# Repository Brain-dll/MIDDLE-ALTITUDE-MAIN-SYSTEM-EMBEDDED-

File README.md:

# technofest-3000-telemetry
This repository was created to improve telemetry system of Ephemeris

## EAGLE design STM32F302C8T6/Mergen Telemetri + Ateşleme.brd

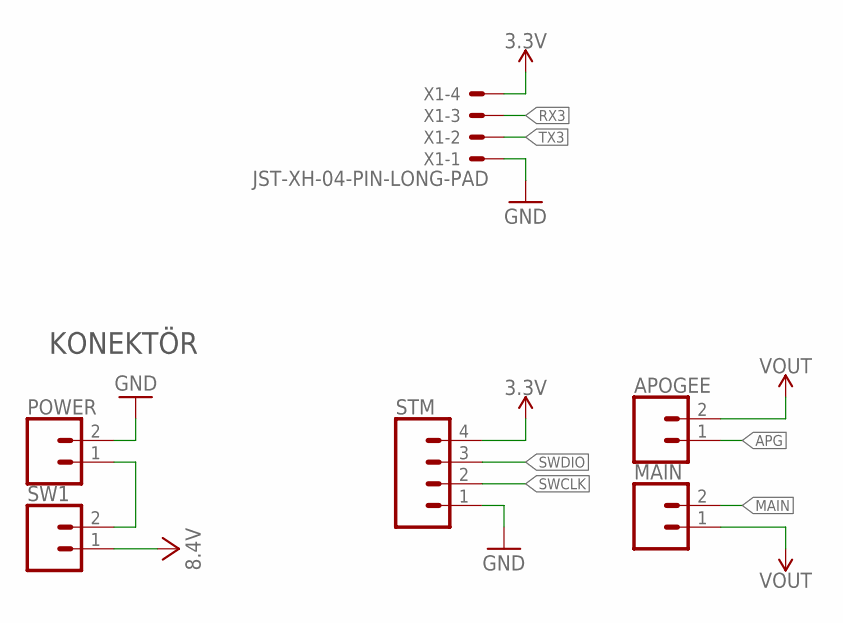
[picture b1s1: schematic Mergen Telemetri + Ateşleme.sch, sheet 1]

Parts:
APOGEE: CONN_023.5MM-NO_SILK; SCREWTERMINAL-3.5MM-2-NS
MAIN: CONN_023.5MM-NO_SILK; SCREWTERMINAL-3.5MM-2-NS
POWER: CONN_023.5MM-NO_SILK; SCREWTERMINAL-3.5MM-2-NS
STM: CONN_04; 1X04
SW1: CONN_023.5MM-NO_SILK; SCREWTERMINAL-3.5MM-2-NS
X1: JST-XH-04-PIN-LONG-PAD; JST-XH-04-PACKAGE-LONG-PAD

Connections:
3.3V: STM.4, X1.4; also elsewhere on the board
APG: APOGEE.1; also elsewhere on the board
GND: POWER.2, STM.1, X1.1; also elsewhere on the board
MAIN: MAIN.2; also elsewhere on the board
unnamed: POWER.1, SW1.2
RX3: X1.3; also elsewhere on the board
SWCLK: STM.2; also elsewhere on the board
SWDIO: STM.3; also elsewhere on the board
TX3: X1.2; also elsewhere on the board
VCC: SW1.1; also elsewhere on the board
VOUT: APOGEE.2, MAIN.1; also elsewhere on the board

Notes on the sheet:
KONEKTÖR

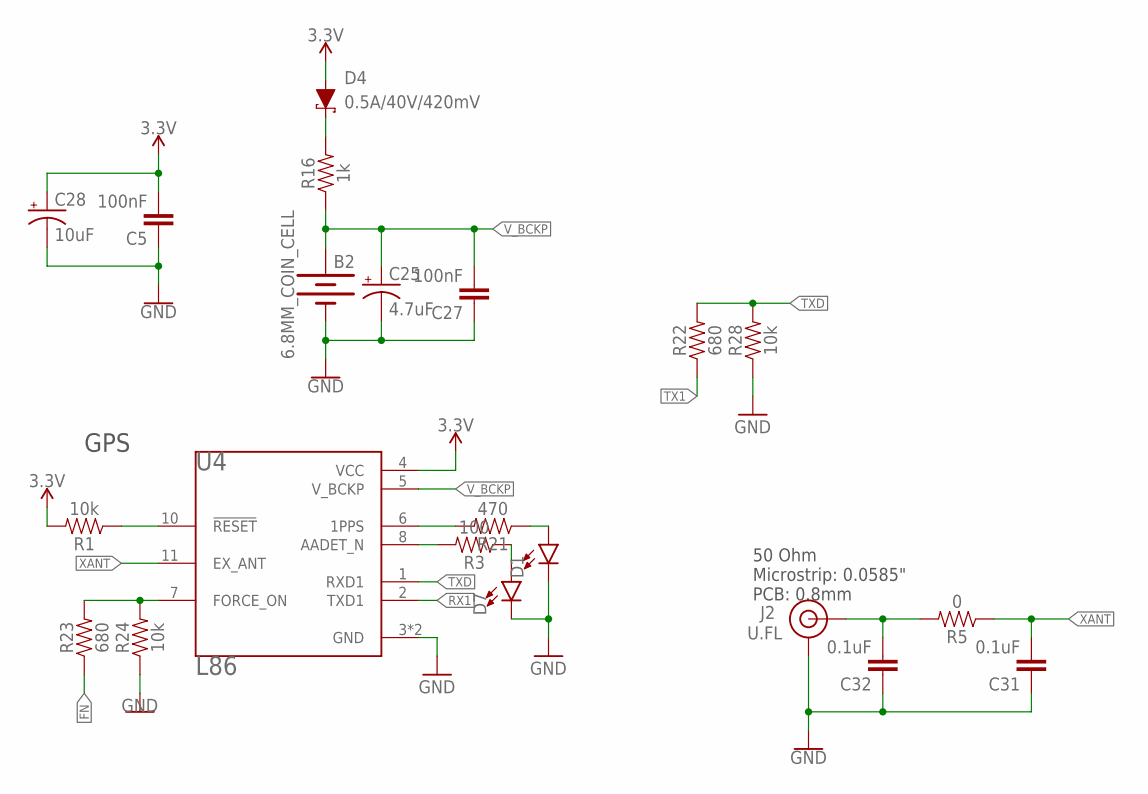
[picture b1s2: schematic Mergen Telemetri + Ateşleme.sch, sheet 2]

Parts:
B2: 6.8MM_COIN_CELL; BATTCON-6.8MM
C5, C27: 100nF; 0603
C25: 4.7uF; EIA3216
C28: 10uF; EIA3216
C31, C32: 0.1uF; 0603
D1, D7: LED0603; LED-0603
D4: 0.5A/40V/420mV; SOD-323
J2: U.FL
R1, R24, R28: 10k; 0603
R3: 100; 0603
R5: 0; 0603
R16: 1k; 0603
R21: 470; 0603
R22, R23: 680; 0603
U4: L86; XCVR_L86

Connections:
3.3V: C5.2, C28.+, D4.A, R1.2, U4.4 (VCC); also elsewhere on the board
FN: R23.1; also elsewhere on the board
GND: B2.-, C5.1, C25.-, C27.1, C28.-, C31.1, C32.1, D1.C, D7.C, J2.1 (GND), J2.2 (GND), R24.1, R28.1, U4.3 (GND), U4.12 (GND); also elsewhere on the board
unnamed: R1.1, U4.10 (!RESET)
unnamed: R21.2, U4.6 (1PPS)
unnamed: D1.A, R21.1
unnamed: D4.C, R16.2
unnamed: R3.2, U4.8 (AADET_N)
unnamed: D7.A, R3.1
unnamed: C32.2, J2.FEED (SIGNAL), R5.2
unnamed: R23.2, R24.2, U4.7 (FORCE_ON)
RX1: U4.2 (TXD1); also elsewhere on the board
TX1: R22.1; also elsewhere on the board
TXD: R22.2, R28.2, U4.1 (RXD1)
V_BCKP: B2.+, C25.+, C27.2, R16.1, U4.5 (V_BCKP)
XANT: C31.2, R5.1, U4.11 (EX_ANT)

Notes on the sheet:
GPS
50 Ohm Microstrip: 0.0585" PCB: 0.8mm

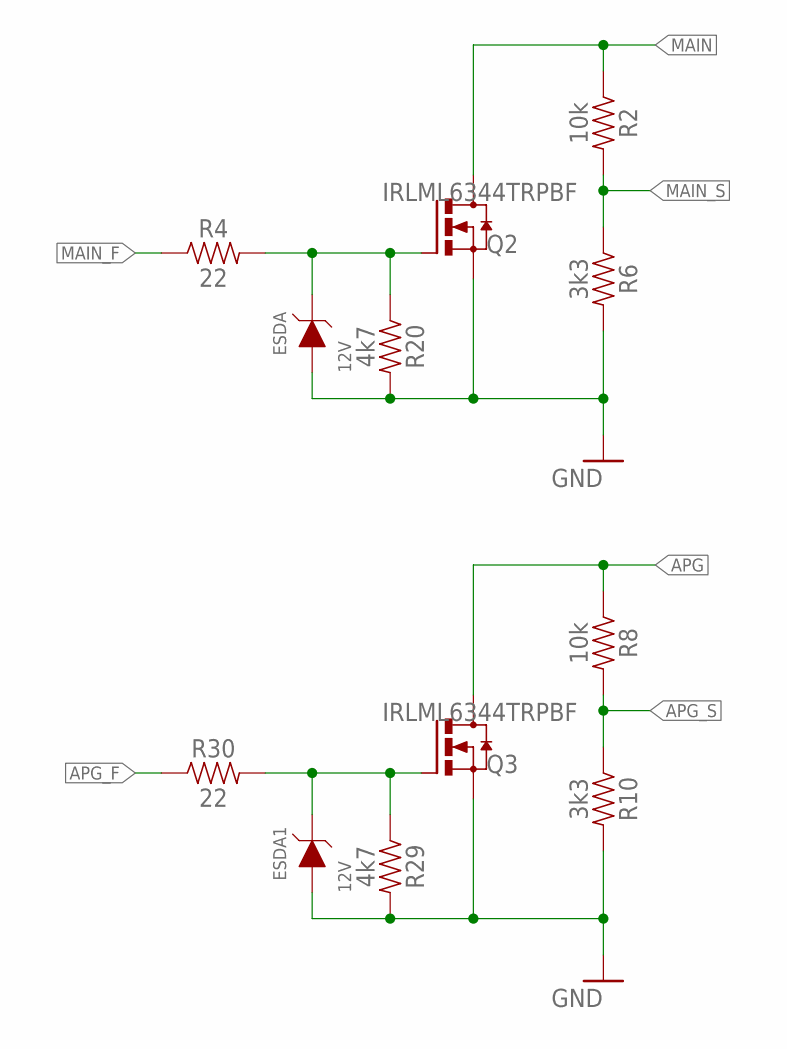
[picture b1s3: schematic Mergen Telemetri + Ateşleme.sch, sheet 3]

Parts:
ESDA, ESDA1: 12V; WE-TVSP_DO-214AC_UNIDIRECTIONAL
Q2, Q3: IRLML6344TRPBF; SOT23
R2, R8: 10k; 0603
R4, R30: 22; 0603
R6, R10: 3k3; 0603
R20, R29: 4k7; 0603

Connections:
APG: Q3.3 (D), R8.1; also elsewhere on the board
APG_F: R30.1; also elsewhere on the board
APG_S: R8.2, R10.1; also elsewhere on the board
GND: ESDA.2 (A), ESDA1.2 (A), Q2.2 (S), Q3.2 (S), R6.2, R10.2, R20.2, R29.2; also elsewhere on the board
MAIN: Q2.3 (D), R2.1; also elsewhere on the board
MAIN_F: R4.1; also elsewhere on the board
MAIN_S: R2.2, R6.1; also elsewhere on the board
unnamed: ESDA1.1 (C), Q3.1 (G), R29.1, R30.2
unnamed: ESDA.1 (C), Q2.1 (G), R4.2, R20.1

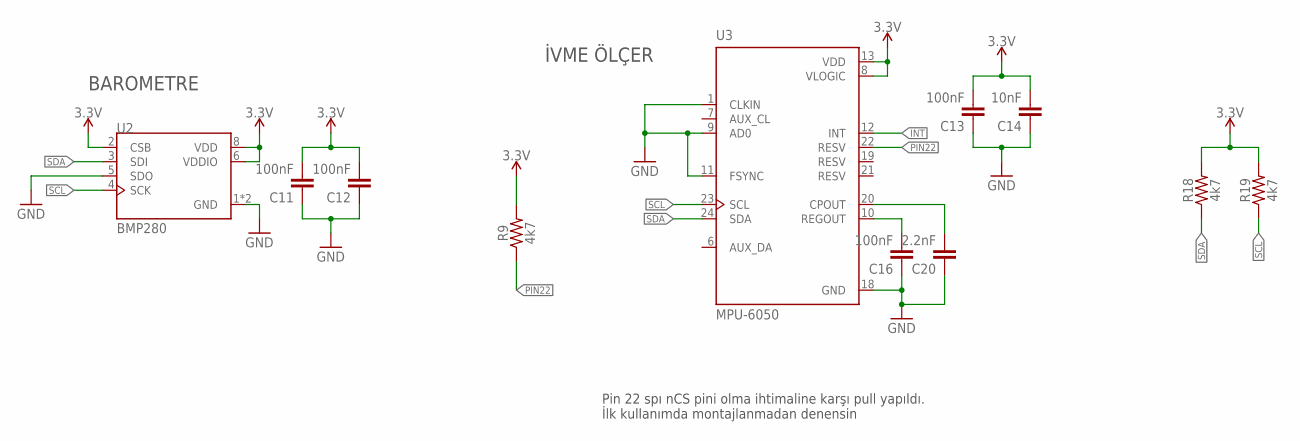
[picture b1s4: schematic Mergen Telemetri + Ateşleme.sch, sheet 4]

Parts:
C11, C12, C13, C16: 100nF; 0603
C14: 10nF; 0603
C20: 2.2nF; 0603
R9, R18, R19: 4k7; 0603
U2: BMP280; XDCR_BMP280
U3: MPU-6050; QFN50P400X400X95-24N

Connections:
3.3V: C11.2, C12.2, C13.2, C14.2, R9.2, R18.2, R19.2, U2.2 (CSB), U2.6 (VDDIO), U2.8 (VDD), U3.8 (VLOGIC), U3.13 (VDD); also elsewhere on the board
GND: C11.1, C12.1, C13.1, C14.1, C16.1, C20.1, U2.1 (GND), U2.5 (SDO), U2.7 (GND), U3.1 (CLKIN), U3.9 (AD0), U3.11 (FSYNC), U3.18 (GND); also elsewhere on the board
INT: U3.12 (INT); also elsewhere on the board
unnamed: C16.2, U3.10 (REGOUT)
unnamed: C20.2, U3.20 (CPOUT)
PIN22: R9.1, U3.22 (RESV)
SCL: R19.1, U2.4 (SCK), U3.23 (SCL); also elsewhere on the board
SDA: R18.1, U2.3 (SDI), U3.24 (SDA); also elsewhere on the board

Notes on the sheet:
İVME ÖLÇER
BAROMETRE
Pin 22 spı nCS pini olma ihtimaline karşı pull yapıldı. İlk kullanımda montajlanmadan denensin

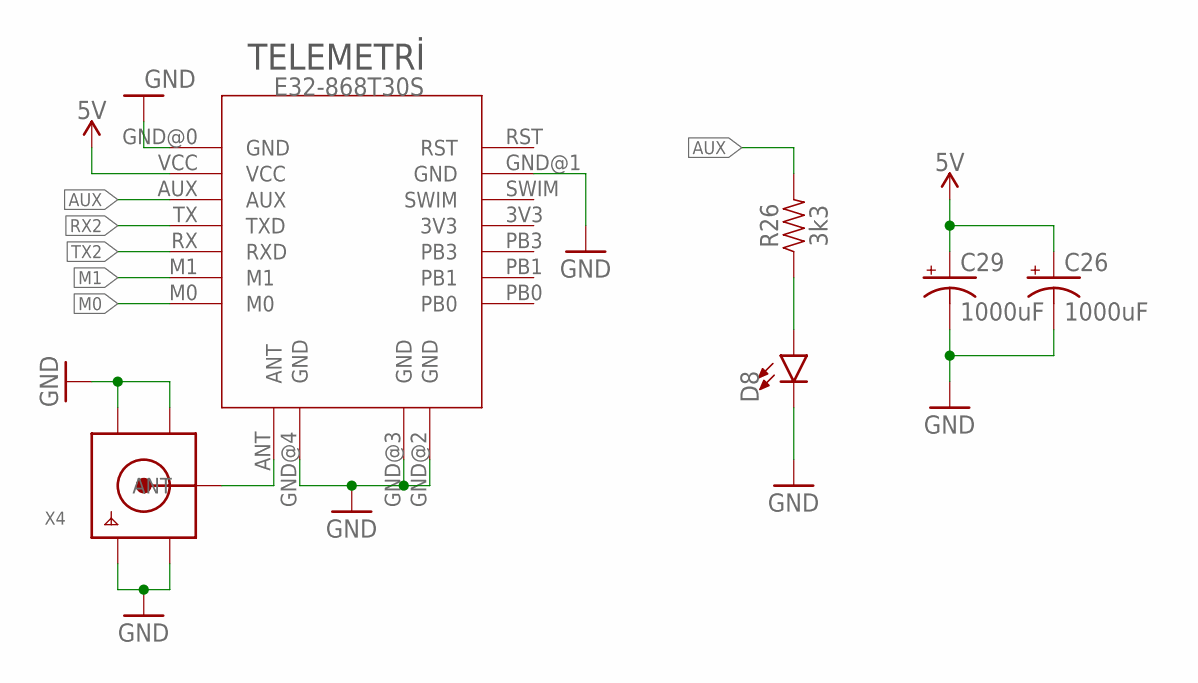
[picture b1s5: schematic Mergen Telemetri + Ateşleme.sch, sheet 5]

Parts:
C26, C29: 1000uF; 150CLZ-1010
D8: LED0603; LED-0603
R26: 3k3; 0603
U5: E32-868T30S
X4: SMACONNECTOR; SMA90_DIP

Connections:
5V: C26.+, C29.+, U5.VCC; also elsewhere on the board
AUX: R26.2, U5.AUX; also elsewhere on the board
GND: C26.-, C29.-, D8.C, U5.GND@0 (GND), U5.GND@1 (GND), U5.GND@2 (GND), U5.GND@3 (GND), U5.GND@4 (GND), X4.GND1, X4.GND2, X4.GND3, X4.GND4; also elsewhere on the board
M0: U5.M0; also elsewhere on the board
M1: U5.M1; also elsewhere on the board
unnamed: U5.ANT, X4.ANTENNA (ANT)
unnamed: D8.A, R26.1
RX2: U5.TX (TXD); also elsewhere on the board
TX2: U5.RX (RXD); also elsewhere on the board

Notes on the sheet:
TELEMETRİ

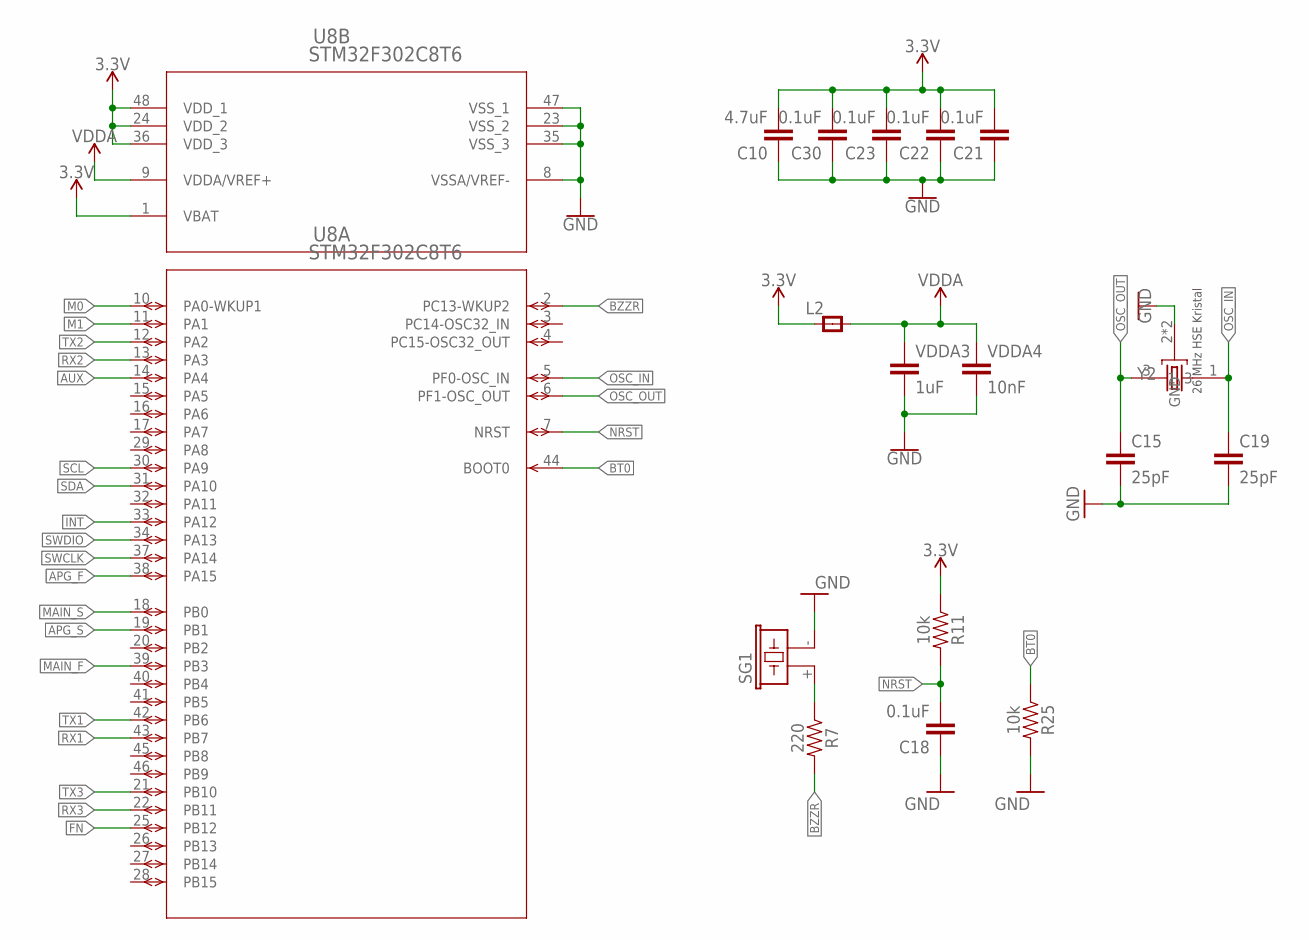
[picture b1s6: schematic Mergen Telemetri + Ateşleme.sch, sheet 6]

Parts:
C10: 4.7uF; 0603
C15, C19: 25pF; 0603
C18, C21, C22, C23, C30: 0.1uF; 0603
L2: RC-MASTER-SMD_FB_0805MP; RC-MASTER-SMD_L0805MP
R7: 220; 0603
R11, R25: 10k; 0603
SG1: F/CM12P
U8: STM32F302C8T6; LQFP48-7X7MM
VDDA3: 1uF; 0603
VDDA4: 10nF; 0603
Y2: ABM3B-26.000MHZ-10-1-U-T; OSCCC500X320X110-4N

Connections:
3.3V: C10.2, C21.2, C22.2, C23.2, C30.2, L2.1, R11.1, U8.1 (VBAT), U8.24 (VDD_2), U8.36 (VDD_3), U8.48 (VDD_1); also elsewhere on the board
APG_F: U8.38 (PA15); also elsewhere on the board
APG_S: U8.19 (PB1); also elsewhere on the board
AUX: U8.14 (PA4); also elsewhere on the board
BT0: R25.1, U8.44 (BOOT0)
BZZR: R7.2, U8.2 (PC13-WKUP2)
FN: U8.25 (PB12); also elsewhere on the board
GND: C10.1, C15.2, C18.1, C19.2, C21.1, C22.1, C23.1, C30.1, R25.2, SG1.- (2), U8.8 (VSSA/VREF-), U8.23 (VSS_2), U8.35 (VSS_3), U8.47 (VSS_1), VDDA3.2, VDDA4.2, Y2.2 (GND), Y2.4 (GND); also elsewhere on the board
INT: U8.33 (PA12); also elsewhere on the board
M0: U8.10 (PA0-WKUP1); also elsewhere on the board
M1: U8.11 (PA1); also elsewhere on the board
MAIN_F: U8.39 (PB3); also elsewhere on the board
MAIN_S: U8.18 (PB0); also elsewhere on the board
unnamed: R7.1, SG1.+ (1)
NRST: C18.2, R11.2, U8.7 (NRST)
OSC_IN: C19.1, U8.5 (PF0-OSC_IN), Y2.1
OSC_OUT: C15.1, U8.6 (PF1-OSC_OUT), Y2.3
RX1: U8.43 (PB7); also elsewhere on the board
RX2: U8.13 (PA3); also elsewhere on the board
RX3: U8.22 (PB11); also elsewhere on the board
SCL: U8.30 (PA9); also elsewhere on the board
SDA: U8.31 (PA10); also elsewhere on the board
SWCLK: U8.37 (PA14); also elsewhere on the board
SWDIO: U8.34 (PA13); also elsewhere on the board
TX1: U8.42 (PB6); also elsewhere on the board
TX2: U8.12 (PA2); also elsewhere on the board
TX3: U8.21 (PB10); also elsewhere on the board
VDDA: L2.2, U8.9 (VDDA/VREF+), VDDA3.1, VDDA4.1

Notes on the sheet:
26 MHz HSE Kristal

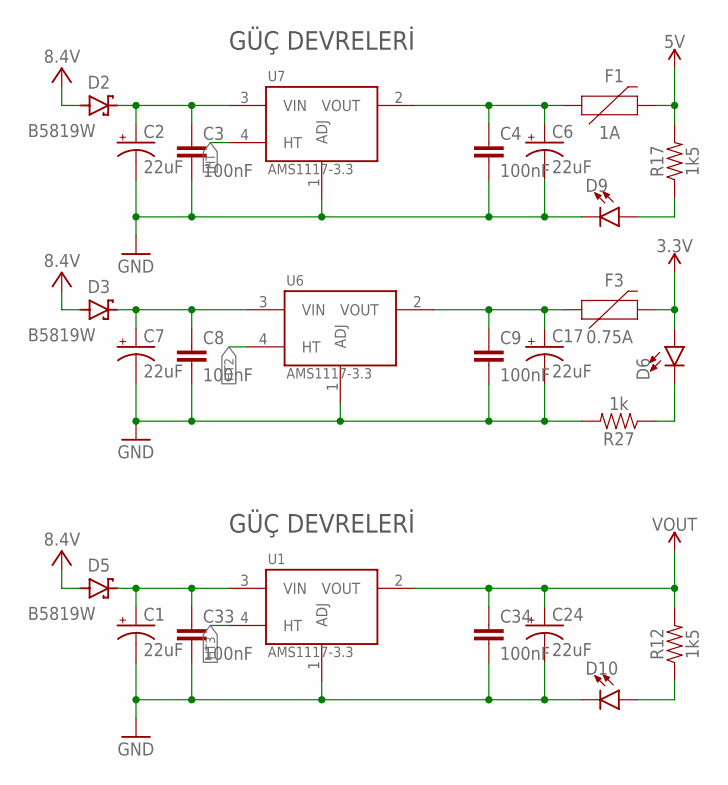
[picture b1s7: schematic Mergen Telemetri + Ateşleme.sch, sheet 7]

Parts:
C1, C2, C6, C7, C17, C24: 22uF; EIA3528
C3, C4, C8, C9, C33, C34: 100nF; 0603
D2, D3, D5: B5819W; SODFL3718X115
D6, D9, D10: LED0603; LED-0603
F1: 1A; 1206
F3: 0.75A; 1206
R12, R17: 1k5; 0603
R27: 1k; 0603
U1, U6, U7: AMS1117-3.3; SOT229P700X180-4N

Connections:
3.3V: D6.A, F3.2; also elsewhere on the board
5V: F1.2, R17.2; also elsewhere on the board
GND: C1.C (-), C2.C (-), C3.2, C4.2, C6.C (-), C7.C (-), C8.2, C9.2, C17.C (-), C24.C (-), C33.2, C34.2, D9.C, D10.C, R27.2, U1.1 (ADJ), U6.1 (ADJ), U7.1 (ADJ); also elsewhere on the board
HT: U7.4 (HT)
HT2: U6.4 (HT)
HT3: U1.4 (HT)
unnamed: C2.A (+), C3.1, D2.1 (C), U7.3 (VIN)
unnamed: C7.A (+), C8.1, D3.1 (C), U6.3 (VIN)
unnamed: C4.1, C6.A (+), F1.1, U7.2 (VOUT)
unnamed: C9.1, C17.A (+), F3.1, U6.2 (VOUT)
unnamed: D9.A, R17.1
unnamed: D6.C, R27.1
unnamed: C1.A (+), C33.1, D5.1 (C), U1.3 (VIN)
unnamed: D10.A, R12.1
VCC: D2.2 (A), D3.2 (A), D5.2 (A); also elsewhere on the board
VOUT: C24.A (+), C34.1, R12.2, U1.2 (VOUT); also elsewhere on the board

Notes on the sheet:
GÜÇ DEVRELERİ

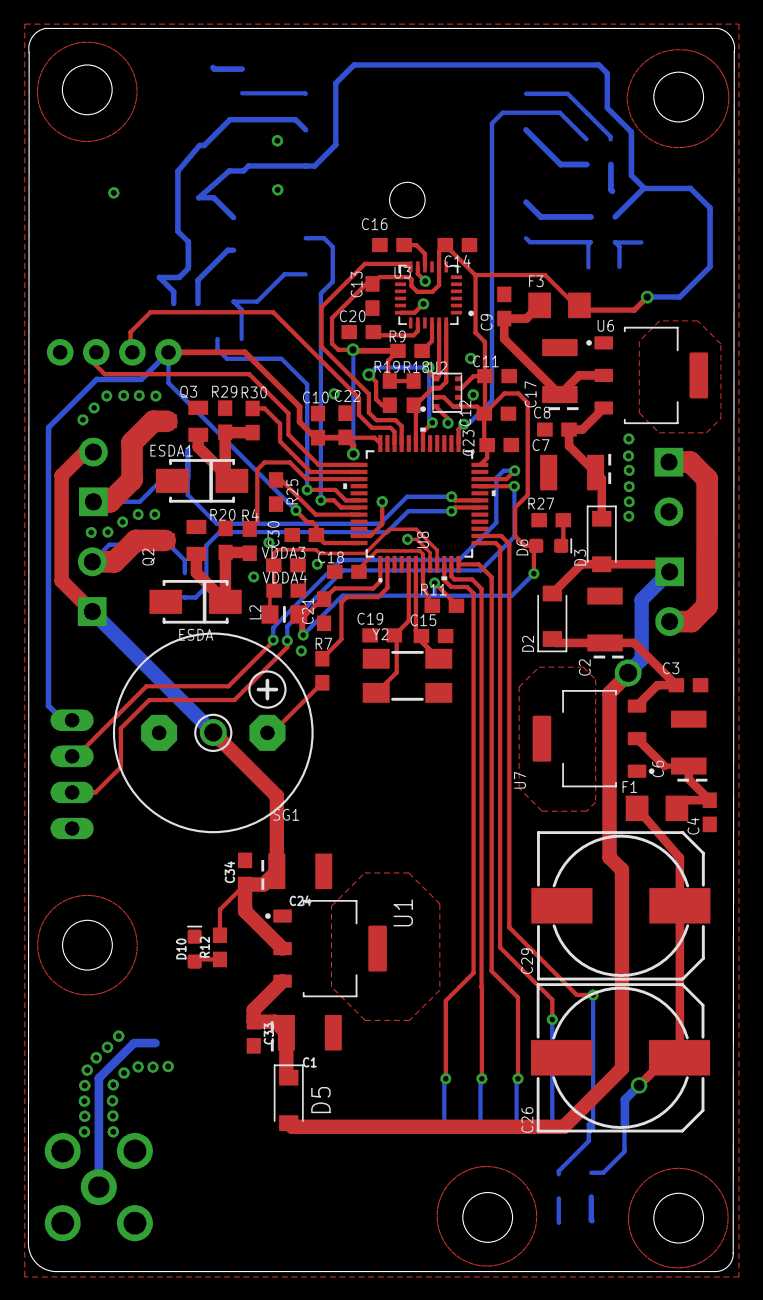
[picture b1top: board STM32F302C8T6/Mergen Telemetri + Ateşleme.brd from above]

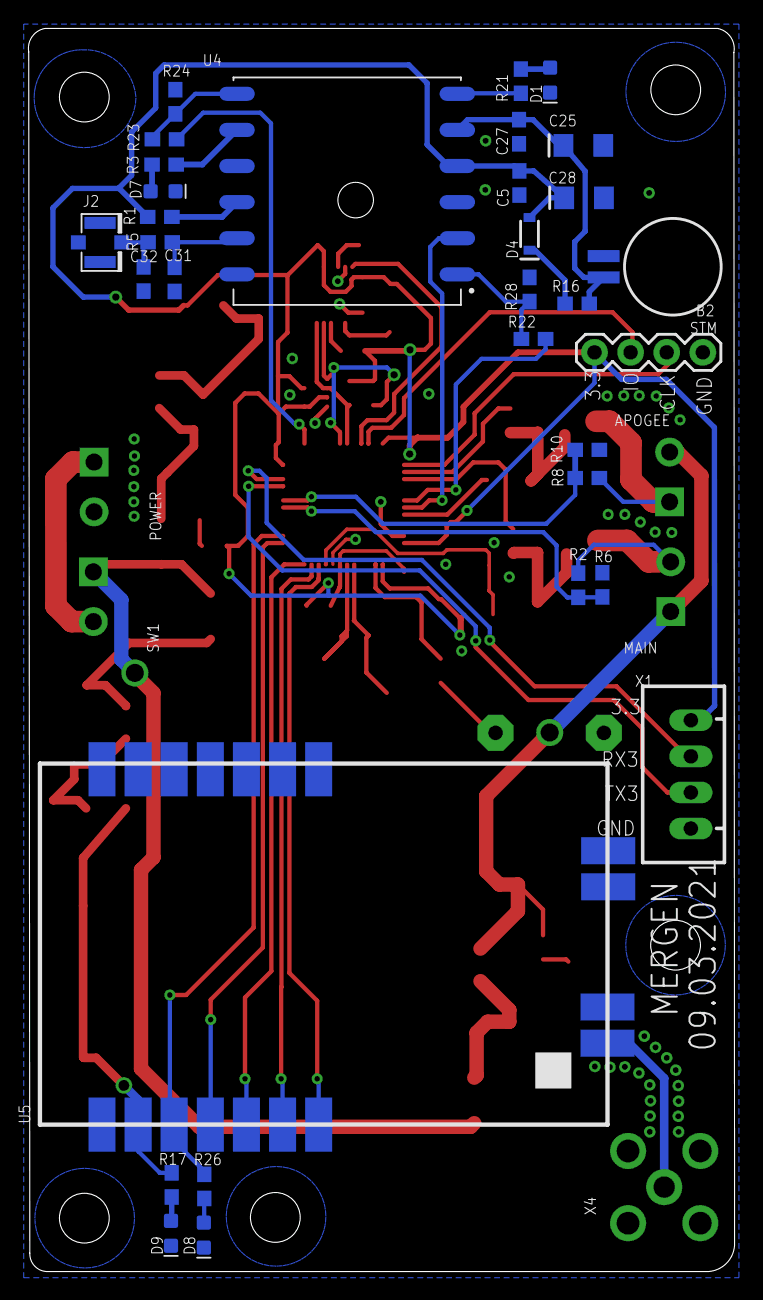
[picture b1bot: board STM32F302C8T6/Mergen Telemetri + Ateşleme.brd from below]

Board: 2 copper layers, 49.7 x 87.5 mm, 99 parts (37 on the bottom side), 60 nets.

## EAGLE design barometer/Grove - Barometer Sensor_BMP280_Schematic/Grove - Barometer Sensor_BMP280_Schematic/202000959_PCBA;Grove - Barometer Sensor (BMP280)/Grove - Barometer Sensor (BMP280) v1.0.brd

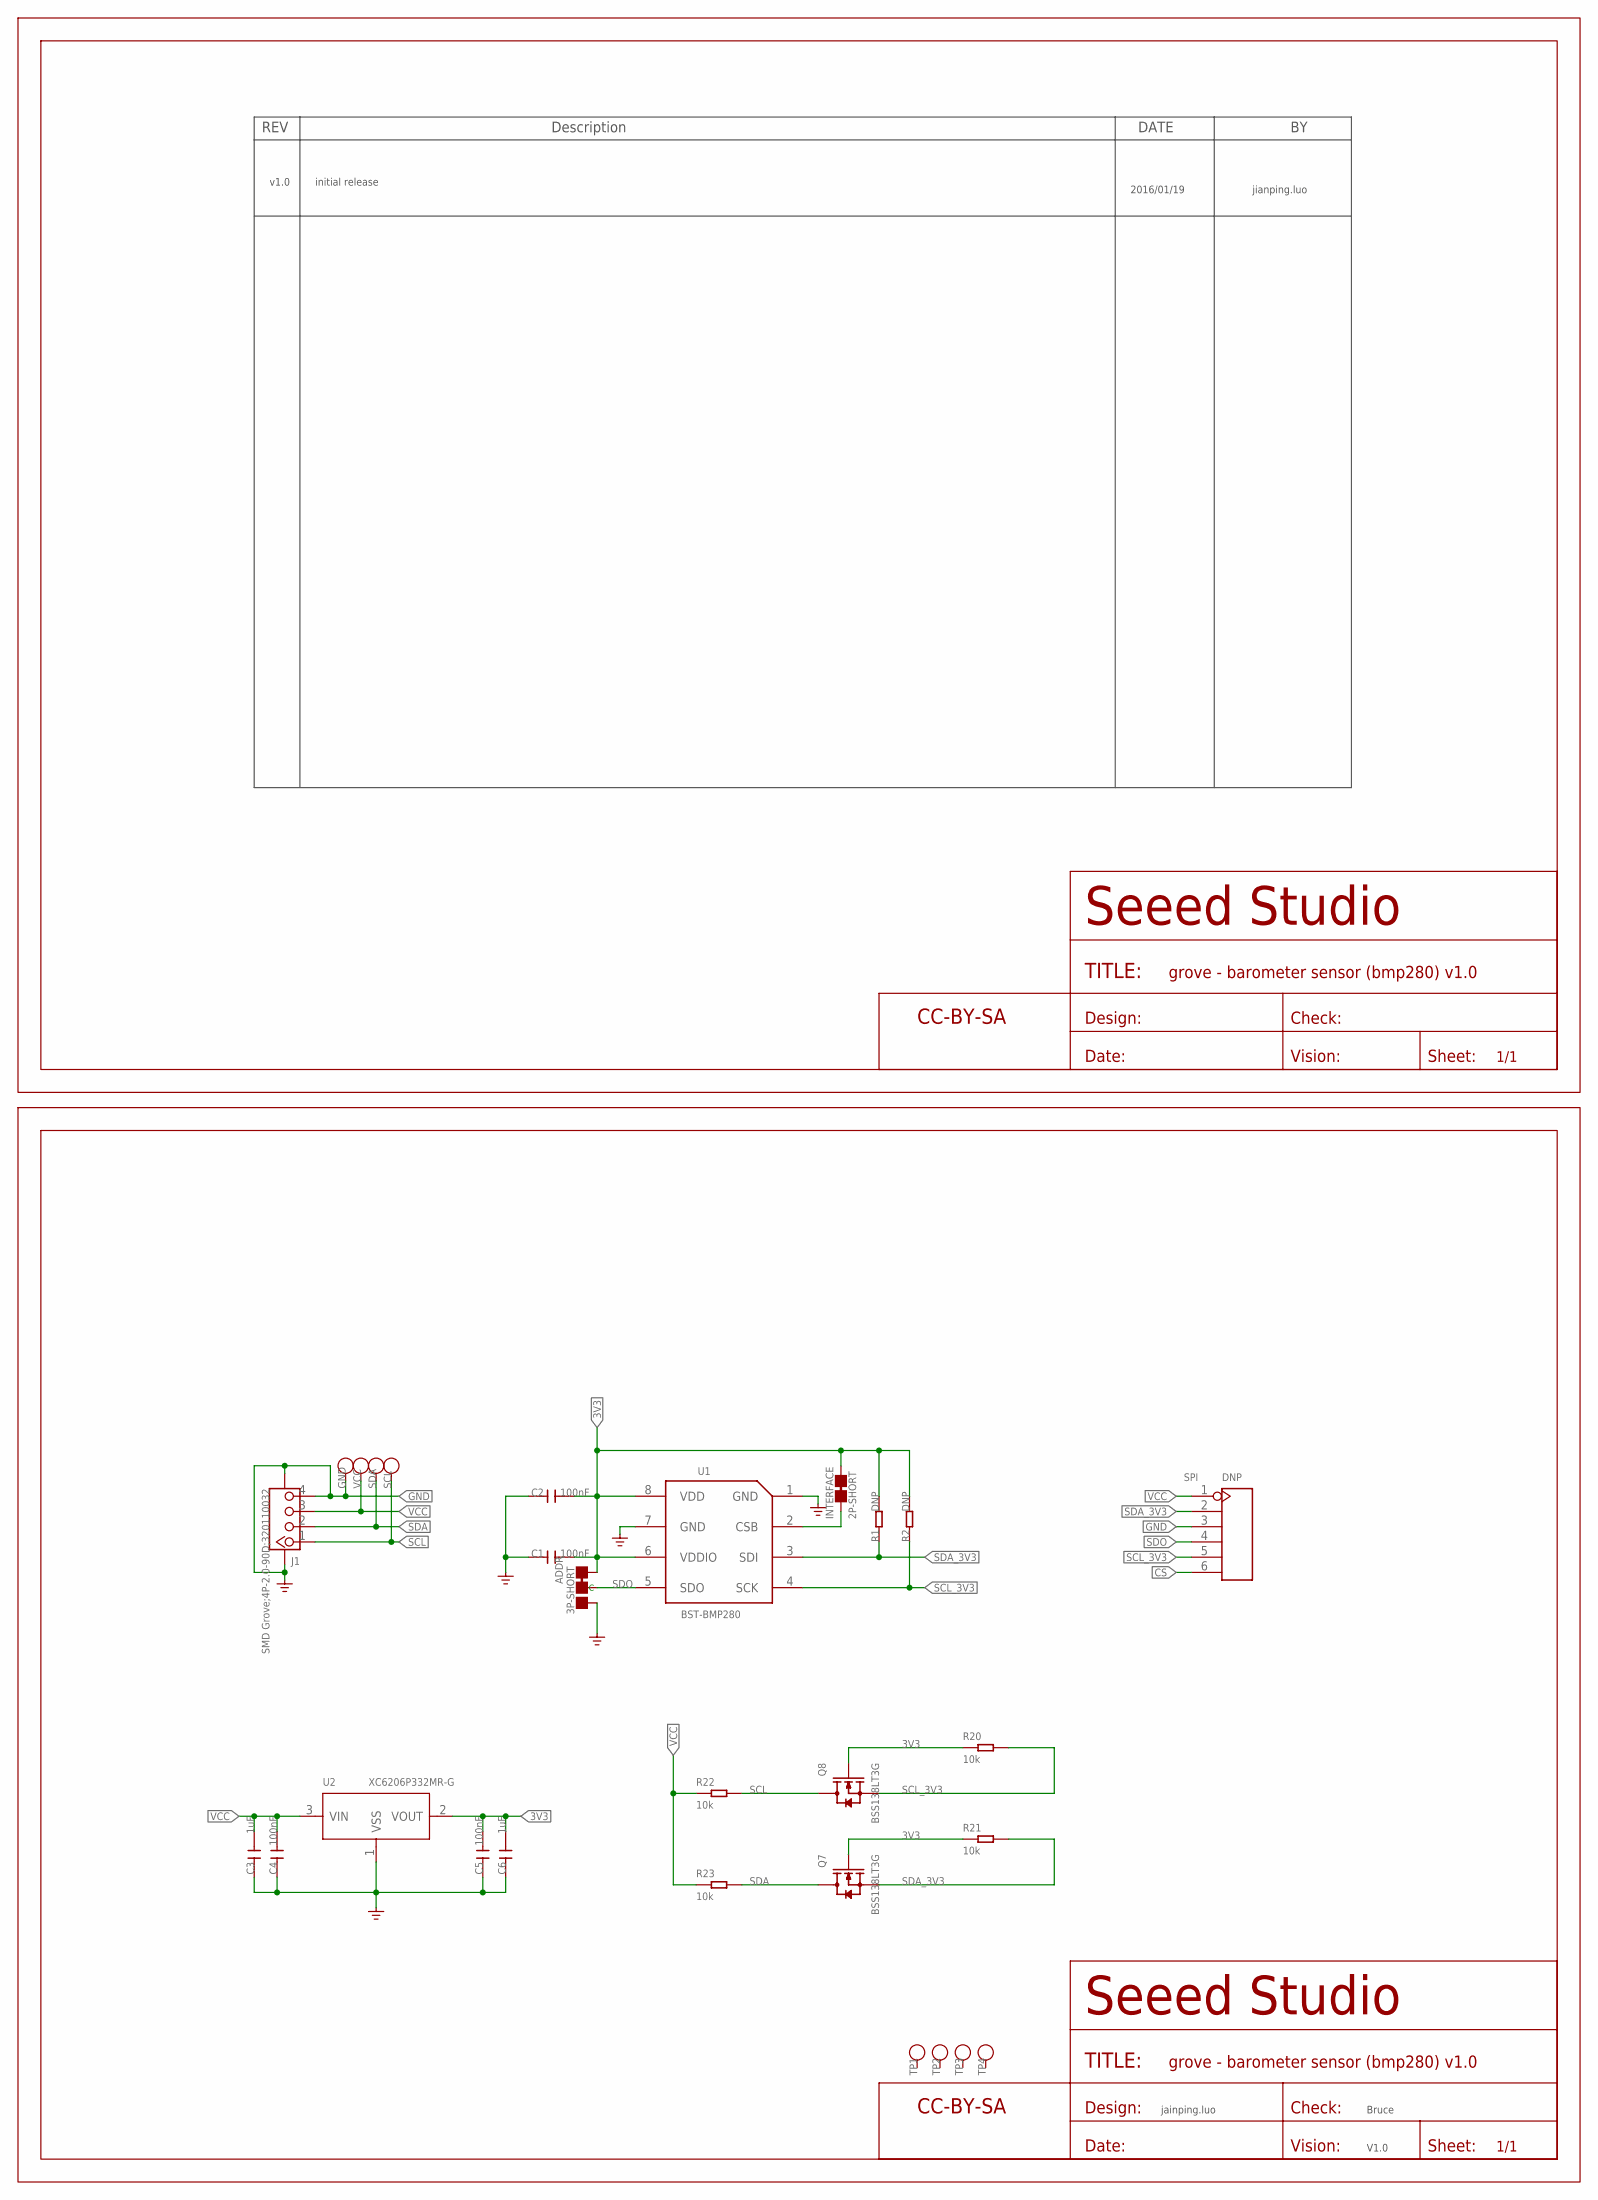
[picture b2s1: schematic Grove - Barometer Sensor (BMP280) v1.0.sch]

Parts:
ADDR: 3P-SHORT; 3P-SMD-SHORT
C1, C2, C4, C5: 100nF; C0603
C3, C6: 1uF; C0603
FR1, FR2: SEEEDSTUDIO-OPEN-SCH-FRAME; SEEEDSTUDIO-PCB-FRAME
GND: TEST-POINT'4545'; TP-D45MIL
INTERFACE: 2P-SHORT; 2P-SMD-SHORT
J1: SMD Grove;4P-2.0-90D;320110032; HW4-SMD-2.0-90D
Q7, Q8: BSS138LT3G; SOT-23
R1, R2: DNP; R0603
R20, R21, R22, R23: 10k; R0603
SCL: TEST-POINT'4545'; TP-D45MIL
SDA: TEST-POINT'4545'; TP-D45MIL
SPI: DNP; H6-2.54-C65D35MIL
TP1, TP2, TP3, TP4: TEST-POINT'4545'; TP-D45MIL
U1: BST-BMP280; LGA8-0.65-2X2.5X0.95MM
U2: XC6206P332MR-G; SOT-23
VCC: TEST-POINT'4545'; TP-D45MIL

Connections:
3V3: ADDR.11 (L), C1.1, C2.1, C5.1, C6.1, INTERFACE.2, Q7.1 (G), Q8.1 (G), R1.2, R2.2, R20.1, R21.1, U1.6 (VDDIO), U1.8 (VDD), U2.2 (VOUT)
CS: INTERFACE.1, SPI.6, U1.2 (CSB)
GND: ADDR.00 (R), C1.2, C2.2, C3.2, C4.2, C5.2, C6.2, GND.T, J1.4, J1.SS1, J1.SS2, SPI.3, U1.1 (GND), U1.7 (GND), U2.1 (VSS)
SCL: J1.1, Q8.3 (D), R22.2, SCL.T
SCL_3V3: Q8.2 (S), R2.1, R20.2, SPI.5, U1.4 (SCK)
SDA: J1.2, Q7.3 (D), R23.2, SDA.T
SDA_3V3: Q7.2 (S), R1.1, R21.2, SPI.2, U1.3 (SDI)
SDO: ADDR.MM (C), SPI.4, U1.5 (SDO)
VCC: C3.1, C4.1, J1.3, R22.1, R23.1, SPI.1, U2.3 (VIN), VCC.T

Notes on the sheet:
v1.0
initial release
2016/01/19
jianping.luo
jainping.luo
Bruce
V1.0

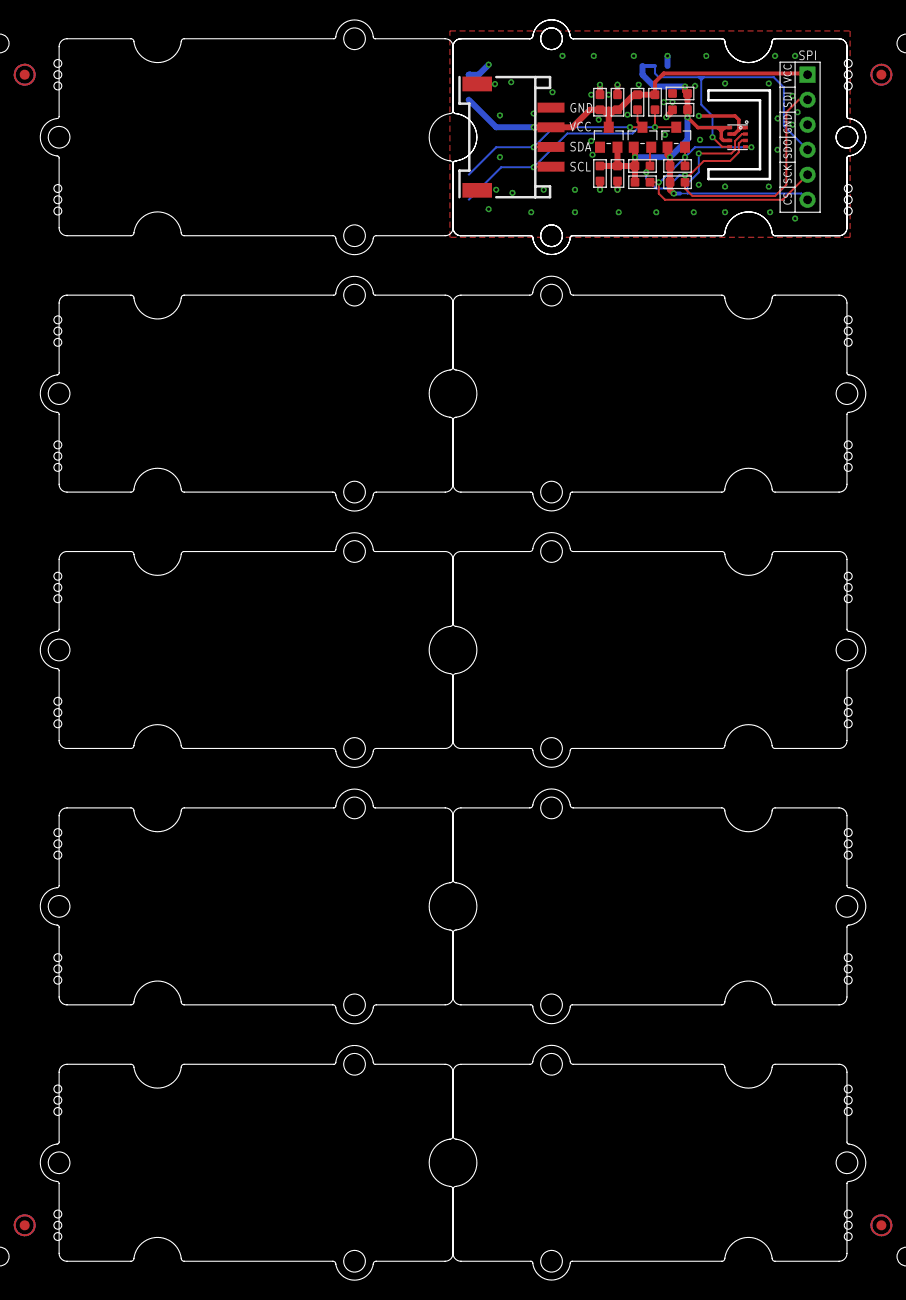
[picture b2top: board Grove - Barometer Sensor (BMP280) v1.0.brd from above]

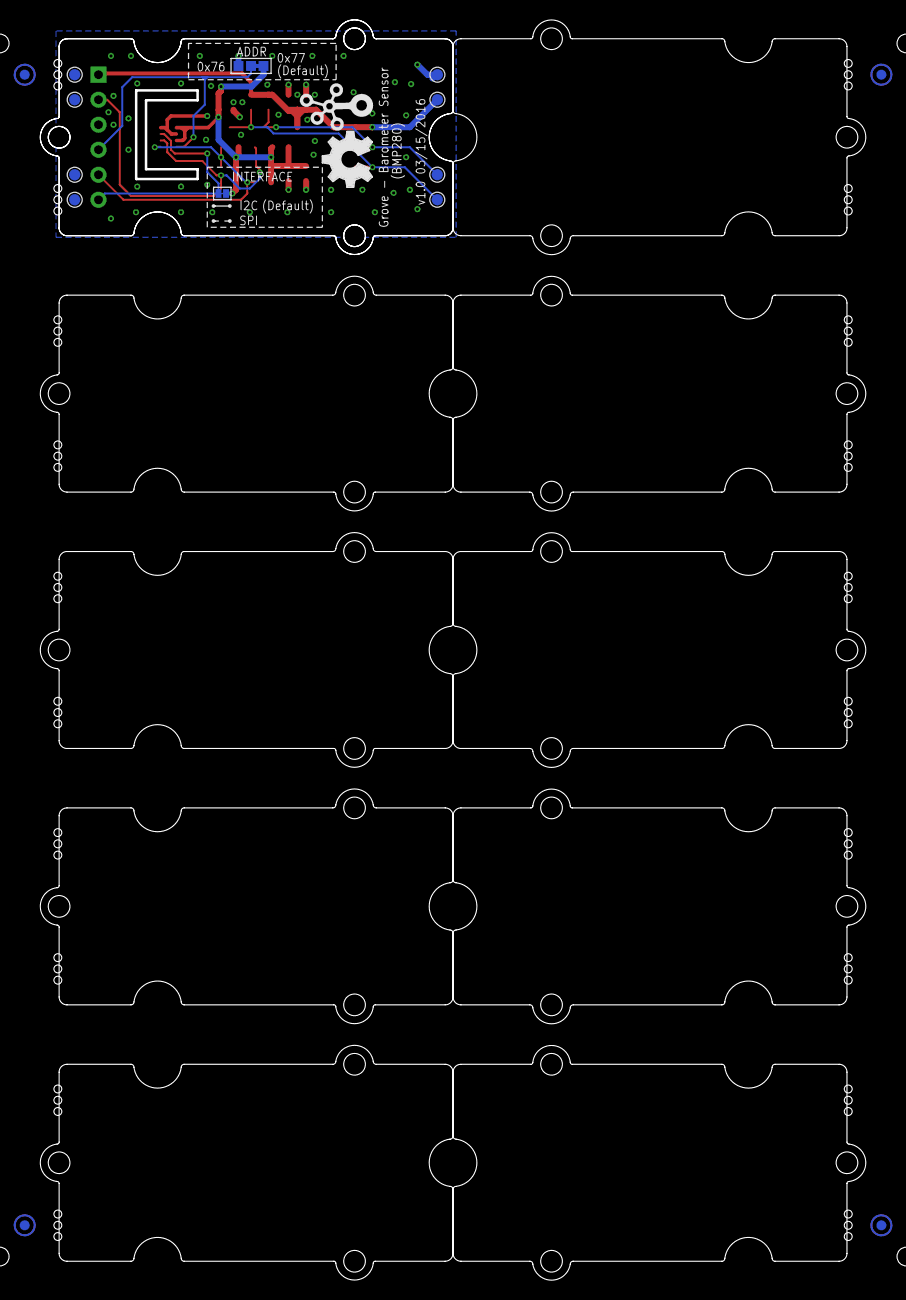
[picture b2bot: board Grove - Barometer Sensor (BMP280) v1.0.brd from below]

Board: 2 copper layers, 83.8 x 128.0 mm, 51 parts (17 on the bottom side), 9 nets.

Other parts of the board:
P1, P2, P3, P4, P5, P6, P7, P8: ROUND-MARK-1.0
U3, U4, U5, U6, U7, U8, U9, U10, U11, U12: GROVE-TEST-PLATFORM
U$3: OSHW_FILLX200_NOTEXT
U$4: TWIGLOGO
U$8: GROVE-1*2-TEST-PLATFORM

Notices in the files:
parts and their libraries:
SparkFun-Fuses: Licensing: Creative Commons ShareAlike 4.0 International - https://creativecommons.org/licenses/by-sa/4.0
Wurth_EMC Components_WE-TVSP: Copyright: Würth Elektronik
STM32F302C8T6: COPYRIGHT: Copyright (C) 2018 Accelerated Designs. All rights reserved
moudle-new: CC-BY-SA
